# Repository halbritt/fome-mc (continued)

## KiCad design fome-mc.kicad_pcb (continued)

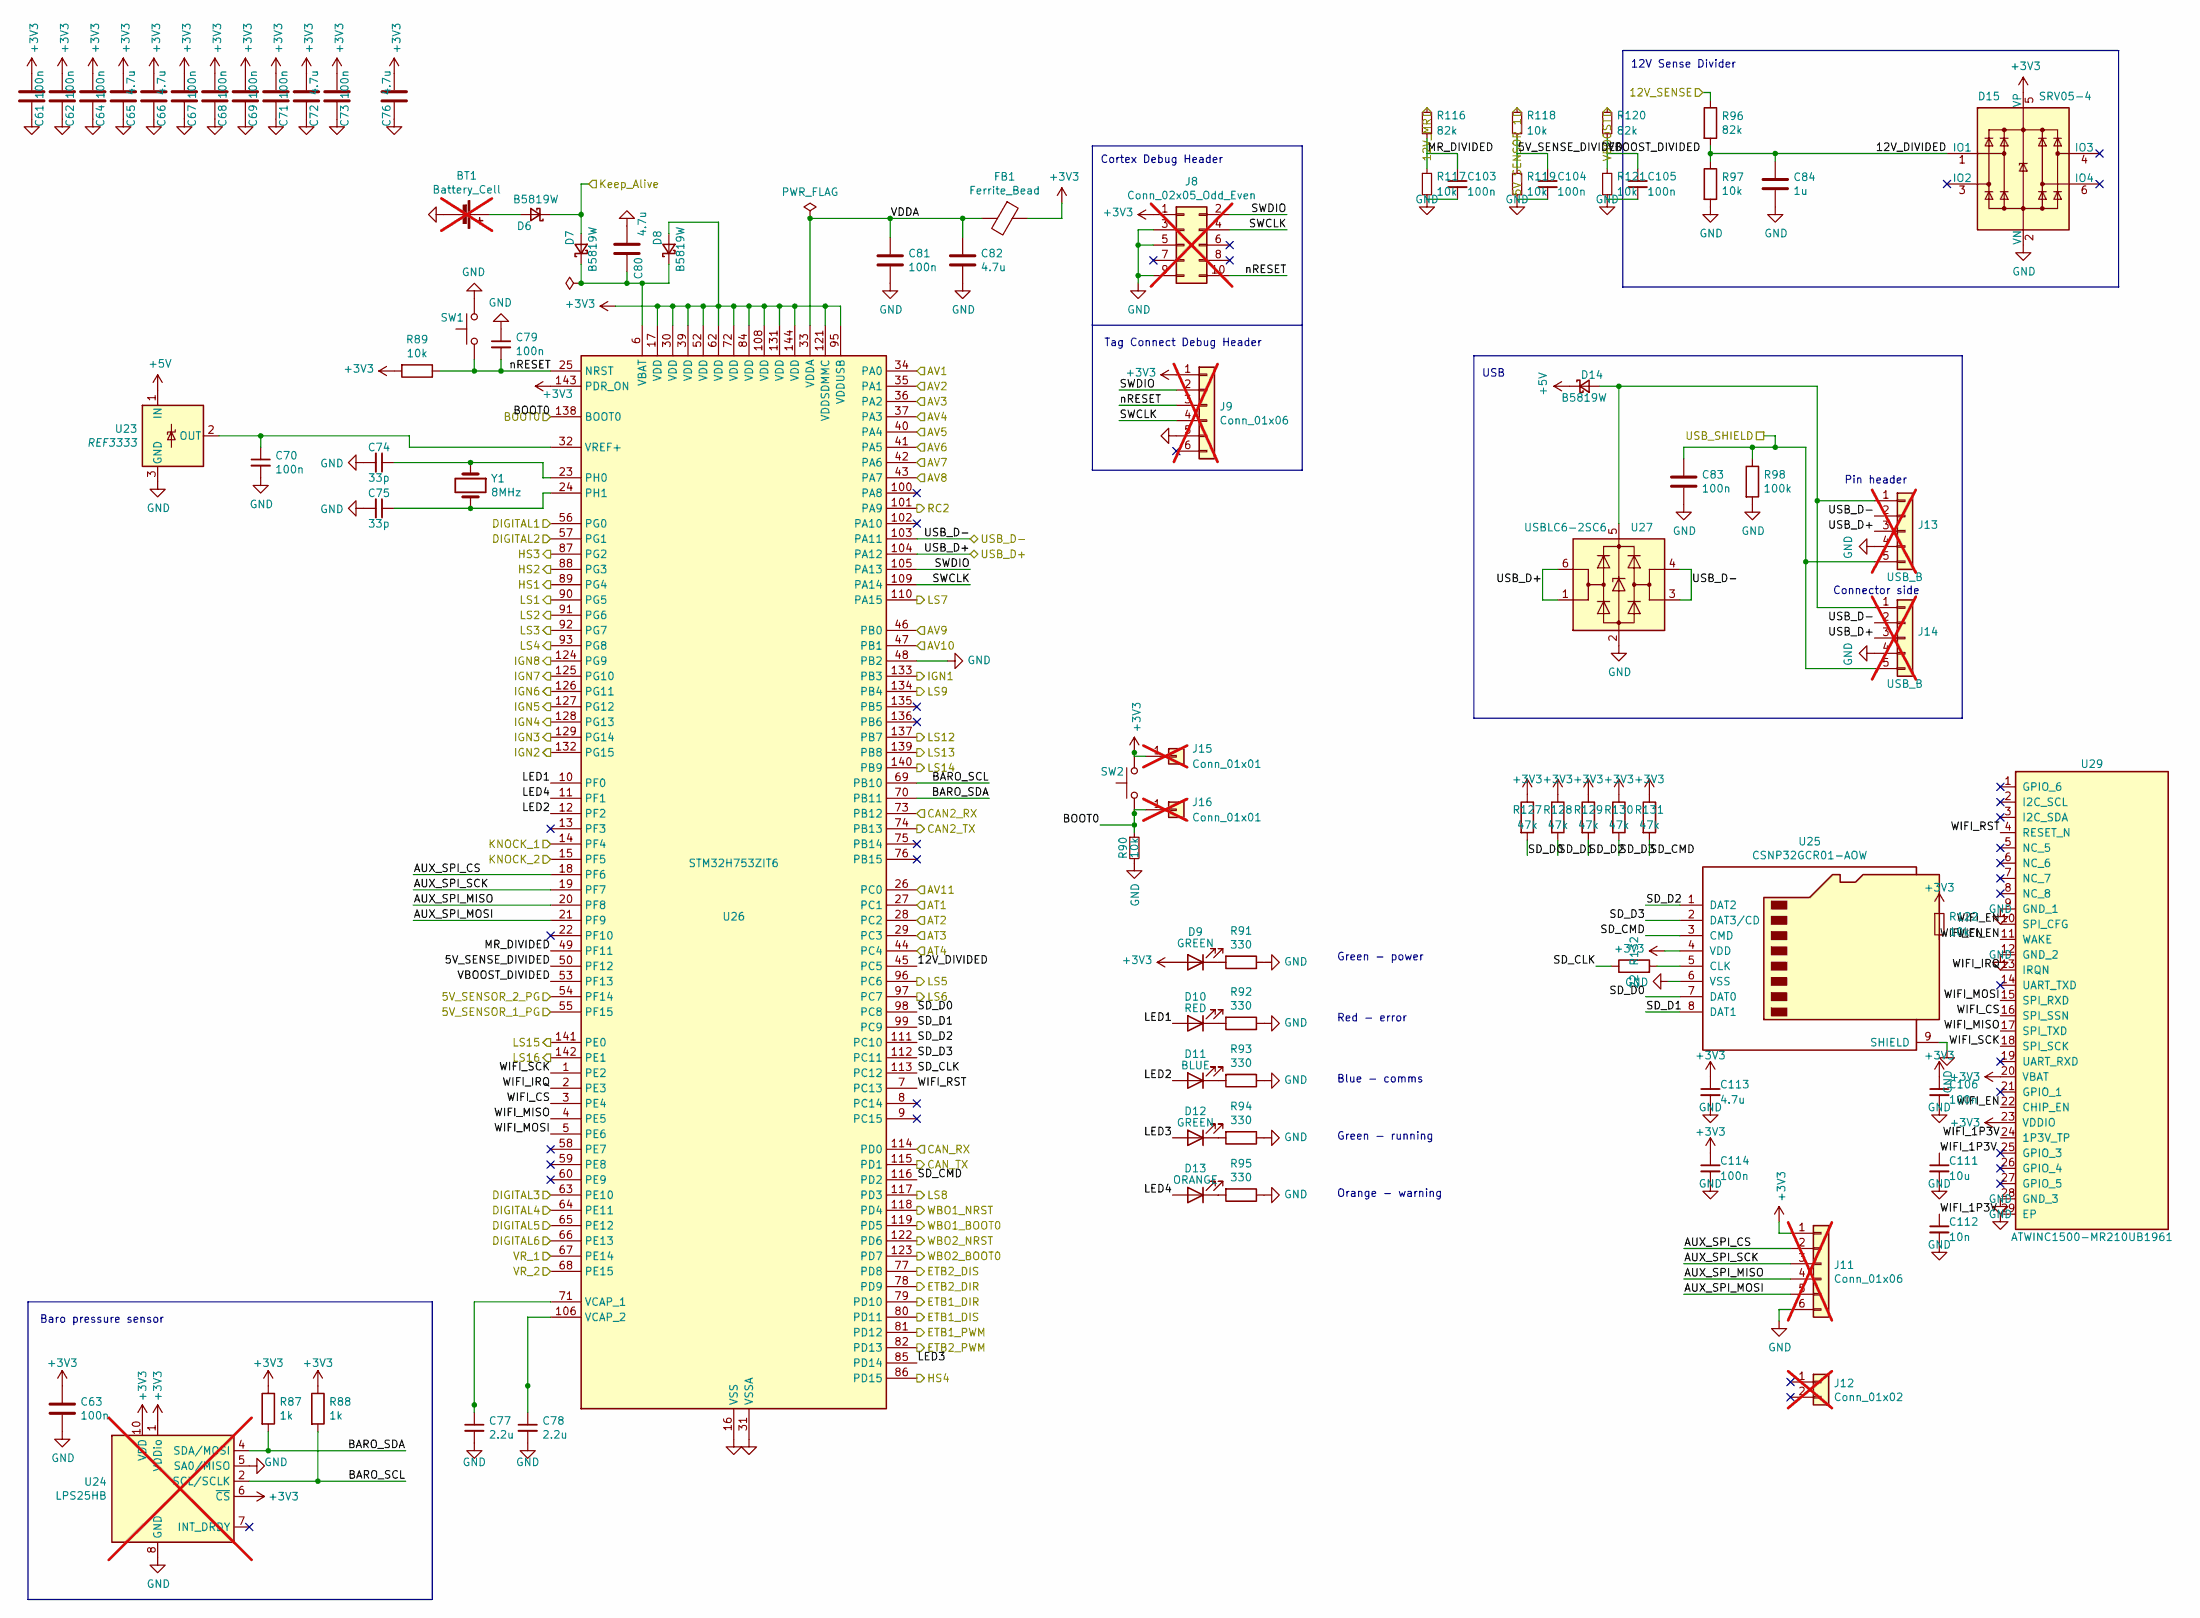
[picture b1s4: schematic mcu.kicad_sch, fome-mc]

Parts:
BT1: Battery_Cell; BatteryHolder_Keystone_1060_1x2032; not fitted
C61, C62, C63, C64, C67, C68, C69, C70, C71, C73, C79, C81, C83, C103, C104, C105, C106, C114: 100n; C_0603_1608Metric; LCSC C161115
C65, C66, C72, C76, C80, C82, C113: 4.7u; C_0603_1608Metric; LCSC C19666
C74, C75: 33p; C_0402_1005Metric; LCSC C1562
C77, C78: 2.2u; C_0603_1608Metric; LCSC C23630
C84: 1u; C_0603_1608Metric; LCSC C15849
C111: 10u; C_0603_1608Metric; LCSC C96446
C112: 10n; C_0603_1608Metric; LCSC C344025
D6, D7, D8, D14: B5819W; D_SOD-123; LCSC C8598
D9, D12: GREEN; LED_0603_1608Metric; LCSC C12624
D10: RED; LED_0603_1608Metric; LCSC C2286
D11: BLUE; LED_0603_1608Metric; LCSC C2288
D13: ORANGE; LED_0603_1608Metric; LCSC C2287
D15: SRV05-4; SOT-23-6; LCSC C85364
FB1: Ferrite_Bead; L_0805_2012Metric; LCSC C1015
J8: Conn_02x05_Odd_Even; PinHeader_2x05_P1.27mm_Vertical_SMD; LCSC N/A; not fitted
J9: Conn_01x06; Tag-Connect_TC2030-IDC-NL_2x03_P1.27mm_Vertical; not fitted
J11: Conn_01x06; PinHeader_1x06_P2.54mm_Vertical; LCSC N/A; not fitted
J12: Conn_01x02; PinHeader_1x02_P2.54mm_Vertical; LCSC N/A; not fitted
J13: USB_B; conn_5_2.5mm; LCSC N/A; not fitted
J14: USB_B; USB_B_TE_5787834_Vertical; LCSC N/A; not fitted
J15, J16: Conn_01x01; PinHeader_1x01_P2.54mm_Vertical; not fitted
R87, R88: 1k; R_0402_1005Metric; LCSC C11702
R89, R90, R97, R117, R118, R119, R121, R122: 10k; R_0402_1005Metric; LCSC C25744
R91, R92, R93, R94, R95: 330; R_0402_1005Metric; LCSC C25104
R96, R116, R120: 82k; R_0603_1608Metric; LCSC C23254
R98: 100k; R_0402_1005Metric; LCSC C25741
R127, R128, R129, R130, R131: 47k; R_0402_1005Metric; LCSC C25792
R132: 22; R_0603_1608Metric; LCSC C23345
SW1, SW2: SW_Push; SW_SPST_EVQQ2; LCSC C318887
U23: REF3333; SOT-23; LCSC C130016
U24: LPS25HB; ST_HLGA-10_2.5x2.5mm_P0.6mm_LayoutBorder3x2y; LCSC C87898; not fitted
U25: CSNP32GCR01-AOW; LGA-8_6x8mm_P1.25mm; LCSC C2841139
U26: STM32H753ZIT6; LQFP-144_20x20mm_P0.5mm; LCSC C730207
U27: USBLC6-2SC6; SOT-23-6; LCSC C7519
U29: ATWINC1500-MR210UB1961; ATWINC1500-MR210UB; LCSC C1558698
Y1: 8MHz; Crystal_SMD_5032-2Pin_5.0x3.2mm; LCSC C115962

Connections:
+3V3: C61.2, C62.2, C63.1, C64.2, C65.2, C66.2, C67.2, C68.2, C69.2, C71.2, C72.2, C73.2, C76.2, C106.1, C113.1, C114.1, D8.2 (A), D9.2 (A), D15.5 (VP), FB1.1, J8.1, J9.1, J11.1, J15.1, R87.1, R88.1, R89.2, R122.1, R127.1, R128.1, R129.1, R130.1, R131.1, SW2.2, U24.1 (VDDio), U24.6 (~CS), U24.10 (VDD), U25.4 (VDD), U26.17 (VDD), U26.30 (VDD), U26.39 (VDD), U26.52 (VDD), U26.62 (VDD), U26.72 (VDD), U26.84 (VDD), U26.95 (VDDUSB), U26.108 (VDD), U26.121 (VDDSDMMC), U26.131 (VDD), U26.143 (PDR_ON), U26.144 (VDD), U29.20 (VBAT), U29.23 (VDDIO); also elsewhere on the board
+5V: D14.1 (K), U23.1 (IN); also elsewhere on the board
/5V_SENSOR_1: R118.1; also elsewhere on the board
/12V_IGN_SW: R96.1; also elsewhere on the board
/12V_MR: R116.1; also elsewhere on the board
/BOOT0_NET: J16.1, R90.1, SW2.1, U26.138 (BOOT0); also elsewhere on the board
/ETB1_DIR: U26.79 (PD10); also elsewhere on the board
/ETB1_DIS: U26.80 (PD11); also elsewhere on the board
/ETB1_PWM: U26.81 (PD12); also elsewhere on the board
/ETB2_DIR: U26.78 (PD9); also elsewhere on the board
/ETB2_DIS: U26.77 (PD8); also elsewhere on the board
/ETB2_PWM: U26.82 (PD13); also elsewhere on the board
/Keep_Alive/Keep_Alive: D6.1 (K), D7.2 (A); also elsewhere on the board
/LS9: U26.134 (PB4); also elsewhere on the board
/LS12: U26.137 (PB7); also elsewhere on the board
/PB8_STEP_EN: U26.139 (PB8); also elsewhere on the board
/RC2: U26.101 (PA9); also elsewhere on the board
/USB_D+: J13.3, J14.3, U26.104 (PA12), U27.1 (I/O1), U27.6 (I/O1); also elsewhere on the board
/USB_D-: J13.2, J14.2, U26.103 (PA11), U27.3 (I/O2), U27.4 (I/O2); also elsewhere on the board
/VBOOST: R120.1; also elsewhere on the board
/WBO1_BOOT0: U26.119 (PD5); also elsewhere on the board
/WBO1_NRST: U26.118 (PD4); also elsewhere on the board
/WBO2_BOOT0: U26.123 (PD7); also elsewhere on the board
/WBO2_NRST: U26.122 (PD6); also elsewhere on the board
/highside_quad/IN1: U26.89 (PG4); also elsewhere on the board
/highside_quad/IN2: U26.88 (PG3); also elsewhere on the board
/highside_quad/IN3: U26.87 (PG2); also elsewhere on the board
/highside_quad/IN4: U26.86 (PD15); also elsewhere on the board
/ign1/IN1: U26.133 (PB3); also elsewhere on the board
/ign1/IN2: U26.132 (PG15); also elsewhere on the board
/ign1/IN3: U26.129 (PG14); also elsewhere on the board
/ign1/IN4: U26.128 (PG13); also elsewhere on the board
/ign2/IN1: U26.127 (PG12); also elsewhere on the board
/ign2/IN2: U26.126 (PG11); also elsewhere on the board
/ign2/IN3: U26.125 (PG10); also elsewhere on the board
/ign2/IN4: U26.124 (PG9); also elsewhere on the board
/knock/FILTERED_1: U26.14 (PF4); also elsewhere on the board
/knock/FILTERED_2: U26.15 (PF5); also elsewhere on the board
/lowside_quad1/IN1: U26.90 (PG5); also elsewhere on the board
/lowside_quad1/IN2: U26.91 (PG6); also elsewhere on the board
/lowside_quad1/IN3: U26.92 (PG7); also elsewhere on the board
/lowside_quad1/IN4: U26.93 (PG8); also elsewhere on the board
/lowside_quad2/IN1: U26.96 (PC6); also elsewhere on the board
/lowside_quad2/IN2: U26.97 (PC7); also elsewhere on the board
/lowside_quad2/IN3: U26.110 (PA15); also elsewhere on the board
/lowside_quad2/IN4: U26.117 (PD3); also elsewhere on the board
/lowside_quad4/IN2: U26.140 (PB9); also elsewhere on the board
/lowside_quad4/IN3: U26.141 (PE0); also elsewhere on the board
/lowside_quad4/IN4: U26.142 (PE1); also elsewhere on the board
/mcu/5V_SENSE_DIVIDED: C104.1, R118.2, R119.1, U26.50 (PF12)
/mcu/5V_SENSOR_1_PG: U26.55 (PF15); also elsewhere on the board
/mcu/5V_SENSOR_2_PG: U26.54 (PF14); also elsewhere on the board
/mcu/12V_DIVIDED: C84.1, D15.1 (IO1), R96.2, R97.1, U26.45 (PC5)
/mcu/AT1: U26.27 (PC1); also elsewhere on the board
/mcu/AT2: U26.28 (PC2); also elsewhere on the board
/mcu/AT3: U26.29 (PC3); also elsewhere on the board
/mcu/AT4: U26.44 (PC4); also elsewhere on the board
/mcu/AUX_SPI_CS: J11.2, U26.18 (PF6)
/mcu/AUX_SPI_MISO: J11.4, U26.20 (PF8)
/mcu/AUX_SPI_MOSI: J11.5, U26.21 (PF9)
/mcu/AUX_SPI_SCK: J11.3, U26.19 (PF7)
/mcu/AV1: U26.34 (PA0); also elsewhere on the board
/mcu/AV2: U26.35 (PA1); also elsewhere on the board
/mcu/AV3: U26.36 (PA2); also elsewhere on the board
/mcu/AV4: U26.37 (PA3); also elsewhere on the board
/mcu/AV5: U26.40 (PA4); also elsewhere on the board
/mcu/AV6: U26.41 (PA5); also elsewhere on the board
/mcu/AV7: U26.42 (PA6); also elsewhere on the board
/mcu/AV8: U26.43 (PA7); also elsewhere on the board
/mcu/AV9: U26.46 (PB0); also elsewhere on the board
/mcu/AV10: U26.47 (PB1); also elsewhere on the board
/mcu/AV11: U26.26 (PC0); also elsewhere on the board
/mcu/BARO_SCL: R88.2, U24.2 (SCL/SCLK), U26.69 (PB10)
/mcu/BARO_SDA: R87.2, U24.4 (SDA/MOSI), U26.70 (PB11)
/mcu/CAN2_RX: U26.73 (PB12); also elsewhere on the board
/mcu/CAN2_TX: U26.74 (PB13); also elsewhere on the board
/mcu/CAN_RX: U26.114 (PD0); also elsewhere on the board
/mcu/CAN_TX: U26.115 (PD1); also elsewhere on the board
/mcu/DIGITAL1: U26.56 (PG0); also elsewhere on the board
/mcu/DIGITAL2: U26.57 (PG1); also elsewhere on the board
/mcu/DIGITAL3: U26.63 (PE10); also elsewhere on the board
/mcu/DIGITAL4: U26.64 (PE11); also elsewhere on the board
/mcu/DIGITAL5: U26.65 (PE12); also elsewhere on the board
/mcu/DIGITAL6: U26.66 (PE13); also elsewhere on the board
/mcu/LED1: D10.2 (A), U26.10 (PF0)
/mcu/LED2: D11.2 (A), U26.12 (PF2)
/mcu/LED3: D12.2 (A), U26.85 (PD14)
/mcu/LED4: D13.2 (A), U26.11 (PF1)
/mcu/MR_DIVIDED: C103.1, R116.2, R117.1, U26.49 (PF11)
/mcu/SD_CLK: R132.1, U26.113 (PC12)
/mcu/SD_CMD: R131.2, U25.3 (CMD), U26.116 (PD2)
/mcu/SD_D0: R127.2, U25.7 (DAT0), U26.98 (PC8)
/mcu/SD_D1: R128.2, U25.8 (DAT1), U26.99 (PC9)
/mcu/SD_D2: R129.2, U25.1 (DAT2), U26.111 (PC10)
/mcu/SD_D3: R130.2, U25.2 (DAT3/CD), U26.112 (PC11)
/mcu/SWCLK: J8.4, J9.4, U26.109 (PA14)
/mcu/SWDIO: J8.2, J9.2, U26.105 (PA13)
/mcu/USB_SHIELD: C83.1, J13.5, J14.5, R98.1
/mcu/VBOOST_DIVIDED: C105.1, R120.2, R121.1, U26.53 (PF13)
/mcu/VDDA: C81.1, C82.1, FB1.2, U26.33 (VDDA)
/mcu/WIFI_1P3V: C111.1, C112.1, U29.24 (1P3V_TP)
/mcu/WIFI_CS: U26.3 (PE4), U29.16 (SPI_SSN)
/mcu/WIFI_EN: R122.2, U29.10 (SPI_CFG), U29.11 (WAKE), U29.22 (CHIP_EN)
/mcu/WIFI_IRQ: U26.2 (PE3), U29.13 (IRQN)
/mcu/WIFI_MISO: U26.4 (PE5), U29.17 (SPI_TXD)
/mcu/WIFI_MOSI: U26.5 (PE6), U29.15 (SPI_RXD)
/mcu/WIFI_RST: U26.7 (PC13), U29.4 (RESET_N)
/mcu/WIFI_SCK: U26.1 (PE2), U29.18 (SPI_SCK)
/mcu/nRESET: C79.2, J8.10, J9.3, R89.1, SW1.1, U26.25 (NRST)
unnamed: BT1.1 (+), D6.2 (A)
unnamed: C80.1, D7.1 (K), D8.1 (K), U26.6 (VBAT)
unnamed: D9.1 (K), R91.2
unnamed: D10.1 (K), R92.2
unnamed: D11.1 (K), R93.2
unnamed: D12.1 (K), R94.2
unnamed: D13.1 (K), R95.2
unnamed: D14.2 (A), J13.1, J14.1, U27.5 (VBUS)
unnamed: C70.1, U23.2 (OUT), U26.32 (VREF+)
unnamed: R132.2, U25.5 (CLK)
unnamed: C74.1, U26.23 (PH0), Y1.1
unnamed: C75.1, U26.24 (PH1), Y1.2
unnamed: C77.1, U26.71 (VCAP_1)
unnamed: C78.1, U26.106 (VCAP_2)

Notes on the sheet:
12V Sense Divider
Green - running
Green - power
Red - error
USB
Tag Connect Debug Header
Blue - comms
Orange - warning
Connector side
Pin header
Cortex Debug Header
Baro pressure sensor

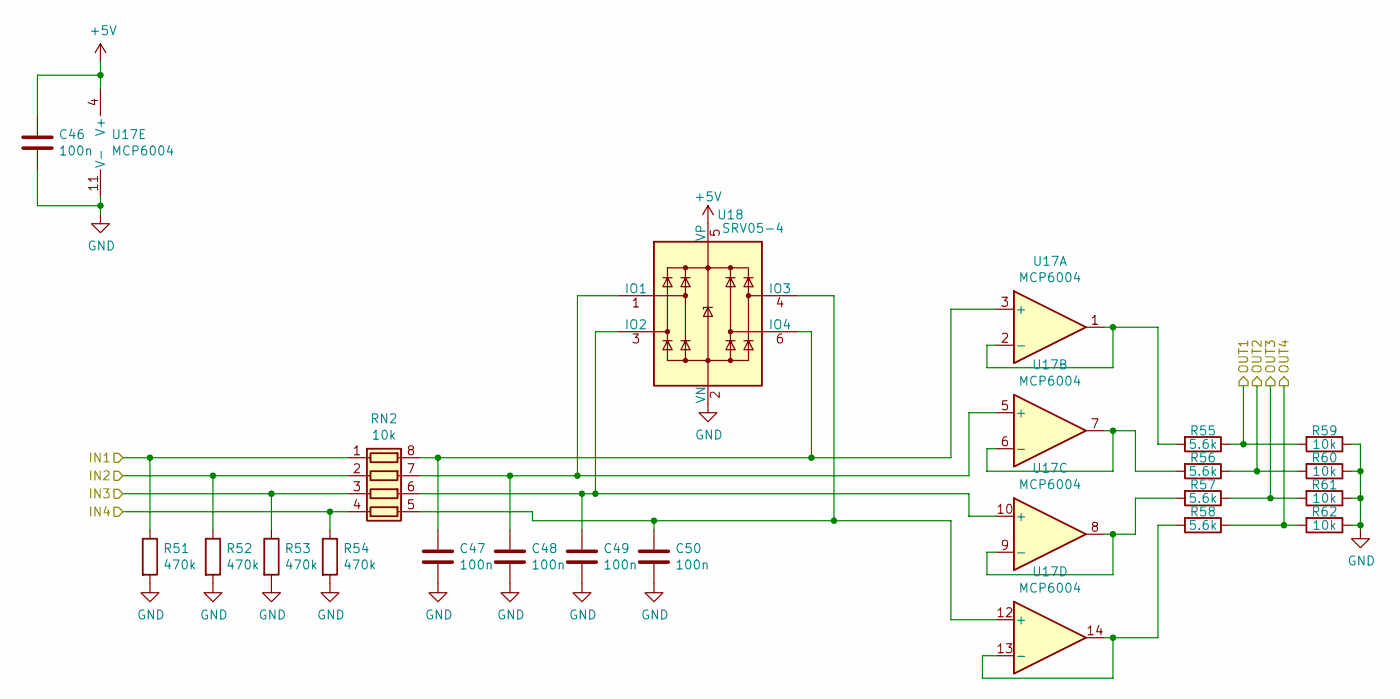
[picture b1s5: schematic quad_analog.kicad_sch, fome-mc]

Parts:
C46: 100n; C_0603_1608Metric; LCSC C161115
C47, C48, C49, C50: 100n; C_0402_1005Metric; LCSC C1525
R51, R52, R53, R54: 470k; R_0402_1005Metric; LCSC C25790
R55, R56, R57, R58: 5.6k; R_0402_1005Metric; LCSC C25908
R59, R60, R61, R62: 10k; R_0402_1005Metric; LCSC C25744
RN2: 10k; R_Array_Convex_4x0603; LCSC C29718
U17: MCP6004; TSSOP-14_4.4x5mm_P0.65mm; LCSC C50282
U18: SRV05-4; SOT-23-6; LCSC C85364

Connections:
+5V: C46.1, U17.4 (V+), U18.5 (VP); also elsewhere on the board
/AV1: R51.1, RN2.1 (R1.1); also elsewhere on the board
/AV2: R52.1, RN2.2 (R2.1); also elsewhere on the board
/AV3: R53.1, RN2.3 (R3.1); also elsewhere on the board
/AV4: R54.1, RN2.4 (R4.1); also elsewhere on the board
/mcu/AV1: R55.1, R59.2; also elsewhere on the board
/mcu/AV2: R56.1, R60.2; also elsewhere on the board
/mcu/AV3: R57.1, R61.2; also elsewhere on the board
/mcu/AV4: R58.1, R62.2; also elsewhere on the board
unnamed: C47.1, RN2.8 (R1.2), U17.3 (+), U18.6 (IO4)
unnamed: C48.1, RN2.7 (R2.2), U17.5 (+), U18.1 (IO1)
unnamed: C49.1, RN2.6 (R3.2), U17.10 (+), U18.3 (IO2)
unnamed: C50.1, RN2.5 (R4.2), U17.12 (+), U18.4 (IO3)
unnamed: R55.2, U17.1, U17.2 (-)
unnamed: R56.2, U17.6 (-), U17.7
unnamed: R57.2, U17.8, U17.9 (-)
unnamed: R58.2, U17.13 (-), U17.14

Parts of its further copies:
C51, C56: 100n; C_0603_1608Metric; LCSC C161115
C52, C53, C54, C55, C57, C58, C59, C60: 100n; C_0402_1005Metric; LCSC C1525
R63, R64, R65, R66, R75, R76, R77, R78: 470k; R_0402_1005Metric; LCSC C25790
R67, R68, R69, R70, R79, R80, R81, R82: 5.6k; R_0402_1005Metric; LCSC C25908
R71, R72, R73, R74, R83, R84, R85, R86: 10k; R_0402_1005Metric; LCSC C25744
RN3, RN4: 10k; R_Array_Convex_4x0603; LCSC C29718
U19, U21: MCP6004; TSSOP-14_4.4x5mm_P0.65mm; LCSC C50282
U20, U22: SRV05-4; SOT-23-6; LCSC C85364

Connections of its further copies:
+5V: C51.1, C56.1, U19.4 (V+), U20.5 (VP), U21.4 (V+), U22.5 (VP); also elsewhere on the board
/AV5: R63.1, RN3.1 (R1.1); also elsewhere on the board
/AV6: R64.1, RN3.2 (R2.1); also elsewhere on the board
/mcu/AV5: R67.1, R71.2; also elsewhere on the board
/mcu/AV6: R68.1, R72.2; also elsewhere on the board
/mcu/AV7: R69.1, R73.2; also elsewhere on the board
/mcu/AV8: R70.1, R74.2; also elsewhere on the board
/mcu/AV9: R79.1, R83.2; also elsewhere on the board
/mcu/AV10: R80.1, R84.2; also elsewhere on the board
/mcu/AV11: R81.1, R85.2; also elsewhere on the board
/quad_analog2/IN3: R65.1, RN3.3 (R3.1)
/quad_analog2/IN4: R66.1, RN3.4 (R4.1)
/quad_analog3/IN1: R75.1, RN4.1 (R1.1)
/quad_analog3/IN2: R76.1, RN4.2 (R2.1)
/quad_analog3/IN3: R77.1, RN4.3 (R3.1)
/quad_analog3/IN4: R78.1, RN4.4 (R4.1)
/quad_analog3/OUT4: R82.1, R86.2
unnamed: C52.1, RN3.8 (R1.2), U19.3 (+), U20.6 (IO4)
unnamed: C53.1, RN3.7 (R2.2), U19.5 (+), U20.1 (IO1)
unnamed: C54.1, RN3.6 (R3.2), U19.10 (+), U20.3 (IO2)
unnamed: C55.1, RN3.5 (R4.2), U19.12 (+), U20.4 (IO3)
unnamed: C57.1, RN4.8 (R1.2), U21.3 (+), U22.6 (IO4)
unnamed: C58.1, RN4.7 (R2.2), U21.5 (+), U22.1 (IO1)
unnamed: C59.1, RN4.6 (R3.2), U21.10 (+), U22.3 (IO2)
unnamed: C60.1, RN4.5 (R4.2), U21.12 (+), U22.4 (IO3)
unnamed: R67.2, U19.1, U19.2 (-)
unnamed: R68.2, U19.6 (-), U19.7
unnamed: R69.2, U19.8, U19.9 (-)
unnamed: R70.2, U19.13 (-), U19.14
unnamed: R79.2, U21.1, U21.2 (-)
unnamed: R80.2, U21.6 (-), U21.7
unnamed: R81.2, U21.8, U21.9 (-)
unnamed: R82.2, U21.13 (-), U21.14

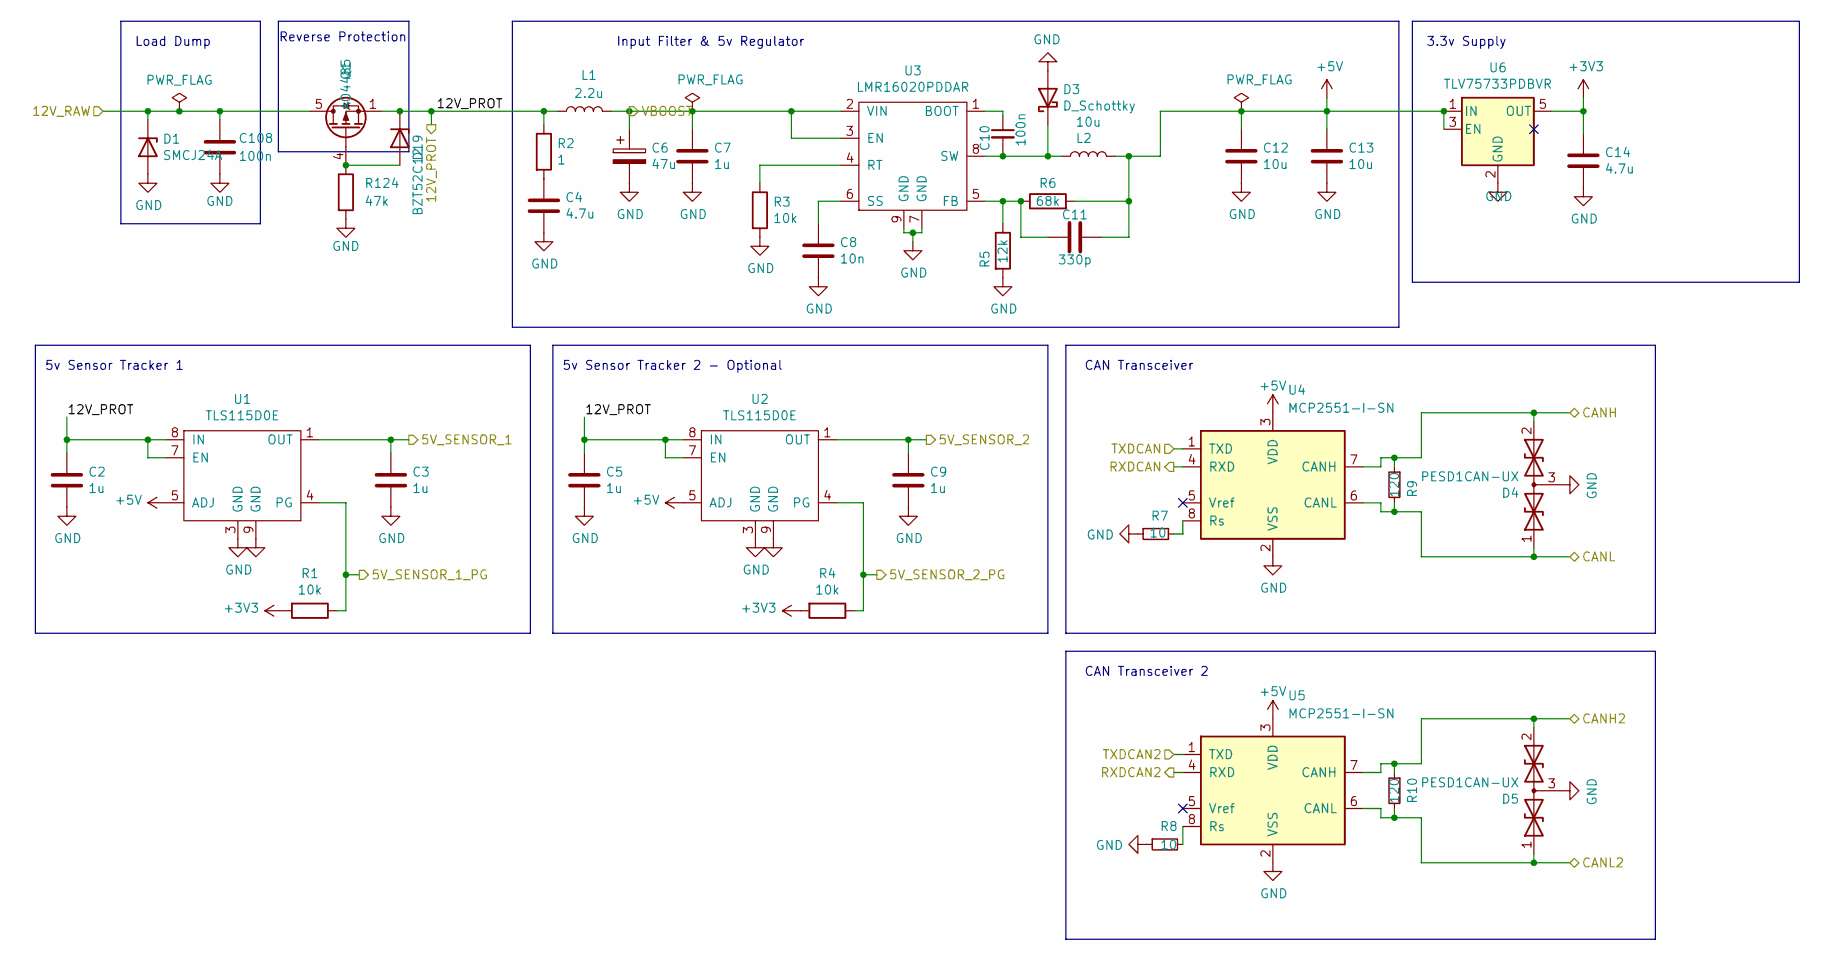
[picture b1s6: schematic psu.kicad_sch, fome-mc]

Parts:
C2, C5, C7: 1u; C_0805_2012Metric; LCSC C354368
C3, C9: 1u; C_0603_1608Metric; LCSC C15849
C4: 4.7u; C_1210_3225Metric; LCSC C417122
C6: 47u; CP_Elec_8x10.5; LCSC C454346
C8: 10n; C_0603_1608Metric; LCSC C344025
C10, C108: 100n; C_0603_1608Metric; LCSC C161115
C11: 330p; C_0402_1005Metric; LCSC C13533
C12: 10u; C_0603_1608Metric; LCSC C96446
C13: 10u; C_1206_3216Metric; LCSC C13585
C14: 4.7u; C_0603_1608Metric; LCSC C19666
D1: SMCJ24A; D_SMC; LCSC C224045
D3: D_Schottky; D_SMA; LCSC C8678
D4, D5: PESD1CAN-UX; SOT-323_SC-70; LCSC C907839
D19: BZT52C12; D_SOD-123; LCSC C43491
L1: 2.2u; L_1210_3225Metric; LCSC C2043220
L2: 10u; MWSA0503; LCSC C408412
Q1: AO4485; SOIC-8_3.9x4.9mm_P1.27mm; LCSC C51499
R1, R3, R4: 10k; R_0402_1005Metric; LCSC C25744
R2: 1; R_0402_1005Metric; LCSC C25086
R5: 12k; R_0402_1005Metric; LCSC C25752
R6: 68k; R_0402_1005Metric; LCSC C36871
R7, R8: 10; R_0603_1608Metric; LCSC C22859
R9, R10: 120; R_0603_1608Metric; LCSC C22787
R124: 47k; R_0603_1608Metric; LCSC C25819
U1, U2: TLS115D0E; Infineon_PG-DSO-8-43; LCSC C3747428
U3: LMR16020PDDAR; SOIC-8-1EP_3.9x4.9mm_P1.27mm_EP2.29x3mm; LCSC C190006
U4, U5: MCP2551-I-SN; SOIC-8_3.9x4.9mm_P1.27mm; LCSC C7376
U6: TLV75733PDBVR; SOT-23-5; LCSC C485517

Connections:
+3V3: C14.1, R1.2, R4.2, U6.5 (OUT); also elsewhere on the board
+5V: C11.1, C12.1, C13.1, L2.2, R6.2, U1.5 (ADJ), U2.5 (ADJ), U4.3 (VDD), U5.3 (VDD), U6.1 (IN), U6.3 (EN); also elsewhere on the board
/5V_SENSOR_1: C3.1, U1.1 (OUT); also elsewhere on the board
/5V_SENSOR_2: C9.1, U2.1 (OUT); also elsewhere on the board
/12V_PROT: C2.1, C5.1, D19.1 (K), L1.1, Q1.1 (S), Q1.2 (S), Q1.3 (S), R2.1, U1.7 (EN), U1.8 (IN), U2.7 (EN), U2.8 (IN)
/12V_RAW: C108.1, D1.1 (A1), Q1.5 (D), Q1.6 (D), Q1.7 (D), Q1.8 (D); also elsewhere on the board
/CAN2+: D5.2 (A2), R10.1, U5.7 (CANH); also elsewhere on the board
/CAN2-: D5.1 (A1), R10.2, U5.6 (CANL); also elsewhere on the board
/CAN+: D4.2 (A2), R9.1, U4.7 (CANH); also elsewhere on the board
/CAN-: D4.1 (A1), R9.2, U4.6 (CANL); also elsewhere on the board
/VBOOST: C6.1, C7.1, L1.2, U3.2 (VIN), U3.3 (EN); also elsewhere on the board
/mcu/5V_SENSOR_1_PG: R1.1, U1.4 (PG); also elsewhere on the board
/mcu/5V_SENSOR_2_PG: R4.1, U2.4 (PG); also elsewhere on the board
/mcu/CAN2_RX: U5.4 (RXD); also elsewhere on the board
/mcu/CAN2_TX: U5.1 (TXD); also elsewhere on the board
/mcu/CAN_RX: U4.4 (RXD); also elsewhere on the board
/mcu/CAN_TX: U4.1 (TXD); also elsewhere on the board
unnamed: C4.1, R2.2
unnamed: C10.2, D3.1 (K), L2.1, U3.8 (SW)
unnamed: D19.2 (A), Q1.4 (G), R124.1
unnamed: C10.1, U3.1 (BOOT)
unnamed: C11.2, R5.1, R6.1, U3.5 (FB)
unnamed: R3.1, U3.4 (RT)
unnamed: C8.1, U3.6 (SS)
unnamed: R7.2, U4.8 (Rs)
unnamed: R8.2, U5.8 (Rs)

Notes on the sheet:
5v Sensor Tracker 1
CAN Transceiver
Load Dump
Input Filter & 5v Regulator
Reverse Protection
3.3v Supply
5v Sensor Tracker 2 - Optional
CAN Transceiver 2

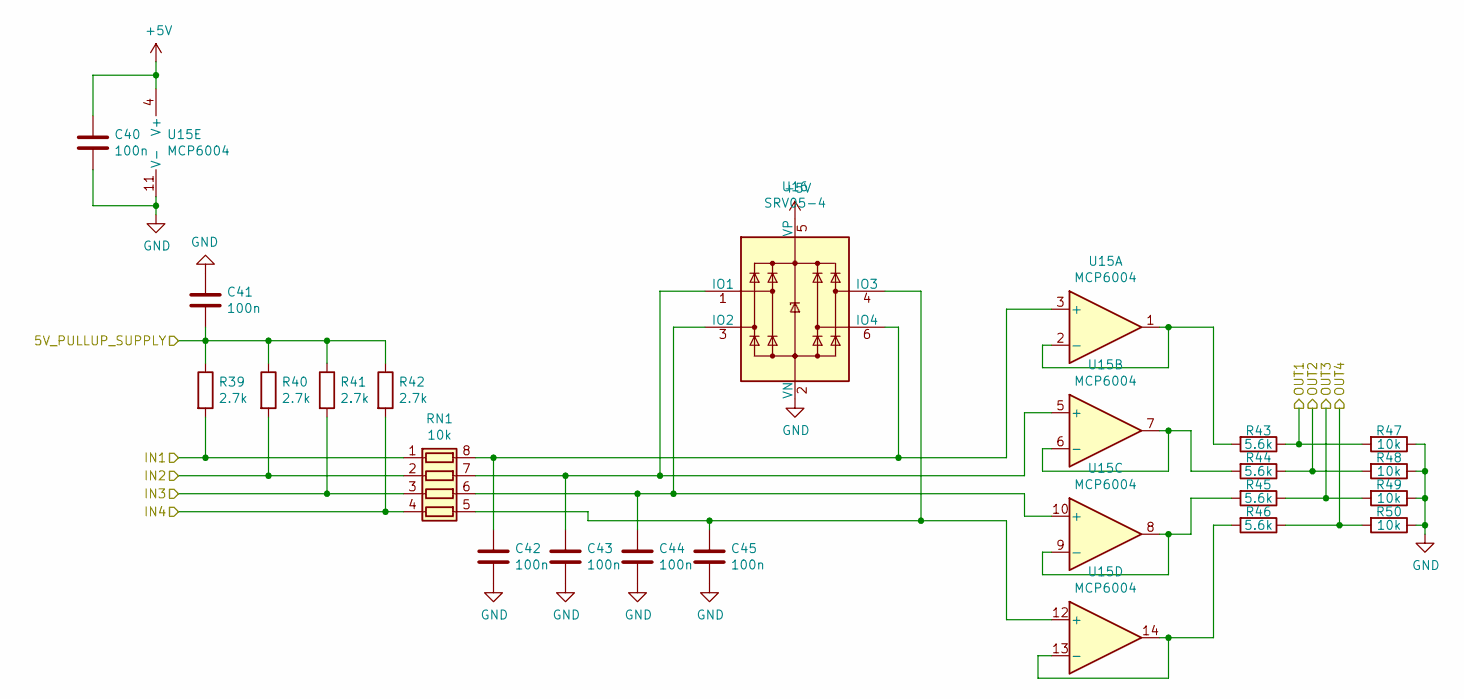
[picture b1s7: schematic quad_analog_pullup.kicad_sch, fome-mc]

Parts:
C40, C41: 100n; C_0603_1608Metric; LCSC C161115
C42, C43, C44, C45: 100n; C_0402_1005Metric; LCSC C1525
R39, R40, R41, R42: 2.7k; R_0603_1608Metric; LCSC C705760
R43, R44, R45, R46: 5.6k; R_0402_1005Metric; LCSC C25908
R47, R48, R49, R50: 10k; R_0402_1005Metric; LCSC C25744
RN1: 10k; R_Array_Convex_4x0603; LCSC C29718
U15: MCP6004; TSSOP-14_4.4x5mm_P0.65mm; LCSC C50282
U16: SRV05-4; SOT-23-6; LCSC C85364

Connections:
+5V: C40.1, U15.4 (V+), U16.5 (VP); also elsewhere on the board
/5V_SENSOR_1: C41.2, R39.1, R40.1, R41.1, R42.1; also elsewhere on the board
/AT1: R39.2, RN1.1 (R1.1); also elsewhere on the board
/AT2: R40.2, RN1.2 (R2.1); also elsewhere on the board
/mcu/AT1: R43.1, R47.2; also elsewhere on the board
/mcu/AT2: R44.1, R48.2; also elsewhere on the board
/mcu/AT3: R45.1, R49.2; also elsewhere on the board
/mcu/AT4: R46.1, R50.2; also elsewhere on the board
/quad_analog_temp/IN3: R41.2, RN1.3 (R3.1)
/quad_analog_temp/IN4: R42.2, RN1.4 (R4.1)
unnamed: C42.1, RN1.8 (R1.2), U15.3 (+), U16.6 (IO4)
unnamed: C43.1, RN1.7 (R2.2), U15.5 (+), U16.1 (IO1)
unnamed: C44.1, RN1.6 (R3.2), U15.10 (+), U16.3 (IO2)
unnamed: C45.1, RN1.5 (R4.2), U15.12 (+), U16.4 (IO3)
unnamed: R43.2, U15.1, U15.2 (-)
unnamed: R44.2, U15.6 (-), U15.7
unnamed: R45.2, U15.8, U15.9 (-)
unnamed: R46.2, U15.13 (-), U15.14

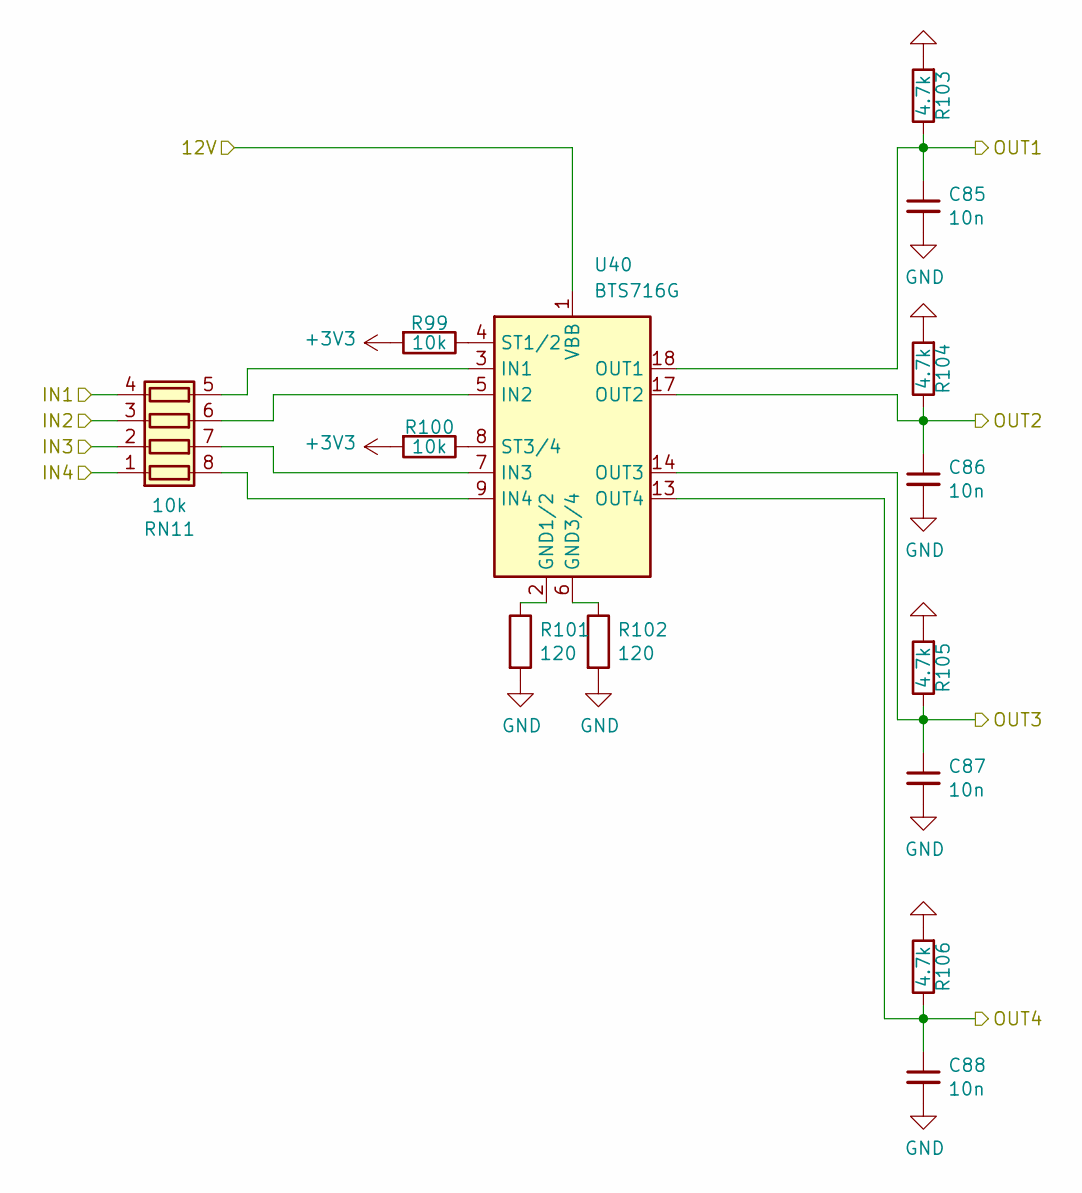
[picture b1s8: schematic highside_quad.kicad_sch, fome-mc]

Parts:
C85, C86, C87, C88: 10n; C_0603_1608Metric; LCSC C344025
R99, R100: 10k; R_0402_1005Metric; LCSC C25744
R101, R102: 120; R_0603_1608Metric; LCSC C22787
R103, R104, R105, R106: 4.7k; R_0805_2012Metric; LCSC C17673
RN11: 10k; R_Array_Convex_4x0603; LCSC C29718
U40: BTS716G; Infineon_PG-DSO-20-32; LCSC C85135

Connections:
+3V3: R99.2, R100.2; also elsewhere on the board
/12V_MR: U40.1 (VBB), U40.10 (VBB), U40.11 (VBB), U40.12 (VBB), U40.15 (VBB), U40.16 (VBB), U40.19 (VBB), U40.20 (VBB); also elsewhere on the board
/highside_quad/IN1: RN11.4 (R4.1); also elsewhere on the board
/highside_quad/IN2: RN11.3 (R3.1); also elsewhere on the board
/highside_quad/IN3: RN11.2 (R2.1); also elsewhere on the board
/highside_quad/IN4: RN11.1 (R1.1); also elsewhere on the board
/highside_quad/OUT1: C85.1, R103.1, U40.18 (OUT1)
/highside_quad/OUT2: C86.1, R104.1, U40.17 (OUT2)
/highside_quad/OUT3: C87.1, R105.1, U40.14 (OUT3)
/highside_quad/OUT4: C88.1, R106.1, U40.13 (OUT4)
unnamed: RN11.8 (R1.2), U40.9 (IN4)
unnamed: RN11.7 (R2.2), U40.7 (IN3)
unnamed: RN11.6 (R3.2), U40.5 (IN2)
unnamed: RN11.5 (R4.2), U40.3 (IN1)
unnamed: R101.1, U40.2 (GND1/2)
unnamed: R102.1, U40.6 (GND3/4)
unnamed: R99.1, U40.4 (ST1/2)
unnamed: R100.1, U40.8 (ST3/4)

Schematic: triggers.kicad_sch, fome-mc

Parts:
C24, C25, C26, C27, C28, C29, C30, C31, C32, C33, C34, C35, C36, C37: 1n; C_0603_1608Metric; LCSC C1588
C38, C39: 100n; C_0603_1608Metric; LCSC C161115
C109, C110: 100n; C_0402_1005Metric; LCSC C1525
R23, R24, R25, R26, R27, R28, R29, R30, R31, R32, R33, R34: 2.7k; R_0603_1608Metric; LCSC C705760
R35, R36, R37, R38, R125, R126: 10k; R_0402_1005Metric; LCSC C25744
U8, U9, U10: SN74LVC2G17DB; SOT-23-6; LCSC C10429
U11, U12: SRV05-4; SOT-23-6; LCSC C85364
U13, U14: MAX9924UAUB+; MSOP-10_3x3mm_P0.5mm; LCSC C143633

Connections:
+3V3: R125.1, R126.1, U8.5 (VCC), U9.5 (VCC), U10.5 (VCC); also elsewhere on the board
+5V: U11.5 (VP), U12.5 (VP); also elsewhere on the board
/5V_SENSOR_1: C38.2, C39.2, C109.1, C110.1, R23.1, R24.1, R25.1, R26.1, R27.1, R28.1, U13.10 (VCC), U14.10 (VCC); also elsewhere on the board
/DIGITAL_1: C24.1, R23.2, R29.2; also elsewhere on the board
/DIGITAL_2: C25.1, R24.2, R30.2; also elsewhere on the board
/DIGITAL_3: C26.1, R25.2, R31.2; also elsewhere on the board
/DIGITAL_4: C27.1, R26.2, R32.2; also elsewhere on the board
/VR1+: R35.1; also elsewhere on the board
/VR1-: R36.1; also elsewhere on the board
/VR2+: R37.1; also elsewhere on the board
/VR2-: R38.1; also elsewhere on the board
/mcu/DIGITAL1: U10.6; also elsewhere on the board
/mcu/DIGITAL2: U8.6; also elsewhere on the board
/mcu/DIGITAL3: U8.4; also elsewhere on the board
/mcu/DIGITAL4: U9.6; also elsewhere on the board
/mcu/DIGITAL5: U10.4; also elsewhere on the board
/mcu/DIGITAL6: U9.4; also elsewhere on the board
/triggers/HALL_IN_5: C28.1, R27.2, R33.2
/triggers/HALL_IN_6: C29.1, R28.2, R34.2
unnamed: C33.1, R32.1, U9.1, U11.1 (IO1), U11.6 (IO4)
unnamed: C35.1, R34.1, U9.3, U11.3 (IO2), U11.4 (IO3)
unnamed: C34.1, R33.1, U10.3, U12.1 (IO1)
unnamed: C30.1, R29.1, U10.1, U12.3 (IO2)
unnamed: C31.1, R30.1, U8.1, U12.4 (IO3)
unnamed: C32.1, R31.1, U8.3, U12.6 (IO4)
unnamed: C36.1, R35.2, U13.1 (IN+)
unnamed: C36.2, R36.2, U13.2 (IN-)
unnamed: C37.1, R37.2, U14.1 (IN+)
unnamed: C37.2, R38.2, U14.2 (IN-)

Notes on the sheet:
74HC parts include internal clamp diodes to the power rails

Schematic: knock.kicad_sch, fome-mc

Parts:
C15: 10n; C_0603_1608Metric; LCSC C344025
C16, C17: 3.3n; C_0805_2012Metric; LCSC C472819
C18, C19: 680p; C_0603_1608Metric; LCSC C1630
C20, C21: 330p; C_0402_1005Metric; LCSC C13533
C22, C23: 47p; C_0402_1005Metric; LCSC C1567
JP1, JP2: Jumper_NO_Small; SolderJumper-2_P1.3mm_Open_TrianglePad1.0x1.5mm; LCSC N/A; not fitted
R11, R12, R21, R22: 33k; R_0402_1005Metric; LCSC C25779
R13, R14, R19, R20: 100k; R_0402_1005Metric; LCSC C25741
R15, R16: 470k; R_0402_1005Metric; LCSC C25790
R17, R18: 12k; R_0402_1005Metric; LCSC C25752
U7: MCP6004; TSSOP-14_4.4x5mm_P0.65mm; LCSC C50282

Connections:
+3V3: R11.2, U7.4 (V+); also elsewhere on the board
/KNOCK_1: C16.2, JP1.1; also elsewhere on the board
/KNOCK_2: C17.2, JP2.1; also elsewhere on the board
/knock/FILTERED_1: C20.2, U7.6 (-), U7.7; also elsewhere on the board
/knock/FILTERED_2: C21.2, U7.8, U7.9 (-); also elsewhere on the board
/knock/V_mid: C15.2, R11.1, R12.1, U7.3 (+), U7.12 (+)
unnamed: C16.1, JP1.2, R13.2
unnamed: C17.1, JP2.2, R14.2
unnamed: C18.2, R17.1, R19.2
unnamed: C19.2, R18.1, R20.2
unnamed: C20.1, R19.1, R21.2
unnamed: C21.1, R20.1, R22.2
unnamed: R15.1, R17.2, U7.1
unnamed: R16.1, R18.2, U7.14
unnamed: R13.1, R15.2, U7.2 (-)
unnamed: C22.2, R21.1, U7.5 (+)
unnamed: C23.2, R22.1, U7.10 (+)
unnamed: R14.1, R16.2, U7.13 (-)

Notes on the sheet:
Short jumper if DC is interesting

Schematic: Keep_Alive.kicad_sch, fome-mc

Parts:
C89: 100n; C_0603_1608Metric; LCSC C161115
C90: 2.2u; C_0603_1608Metric; LCSC C23630
D16, D17: B5819W; D_SOD-123; LCSC C8598
D20, D21: B340A-13-F; D_SMA; LCSC C85098
D22: SMCJ24A; D_SMC; LCSC C224045
IC1: PSM712-LF-T7; SOT-23; Manufacturer_Part_Number PSM712-LF-T7; LCSC C32677
R107: 4.7k; R_0805_2012Metric; LCSC C17673
U41: MIC5205-3.3YM5; SOT-23-5; LCSC C37970

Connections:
/12V_IGN_SW: D20.2 (A); also elsewhere on the board
/12V_MR: D21.2 (A), D22.1 (K); also elsewhere on the board
/12V_RAW: D20.1 (K), D21.1 (K); also elsewhere on the board
/Keep_Alive/Keep_Alive: D17.1 (K); also elsewhere on the board
/Perm_Live: D16.2 (A); also elsewhere on the board
unnamed: D16.1 (K), R107.1
unnamed: C90.2, D17.2 (A), U41.5 (OUT)
unnamed: C89.1, IC1.1 (I/O_1), R107.2, U41.1 (IN), U41.3 (EN)

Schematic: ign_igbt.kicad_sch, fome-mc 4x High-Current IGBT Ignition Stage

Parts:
Q201, Q202, Q203, Q204: FGD3040G2-F085; TO-252-2; LCSC C606124
R201, R202, R203, R204: 15R; R_0603_1608Metric; LCSC C22810
R205, R206, R207, R208: 10k; R_0402_1005Metric; LCSC C25744

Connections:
/IGN1: R201.1; also elsewhere on the board
/IGN1_COIL: Q201.2 (C); also elsewhere on the board
/IGN2: R202.1; also elsewhere on the board
/IGN2_COIL: Q202.2 (C); also elsewhere on the board
/IGN3: R203.1; also elsewhere on the board
/IGN3_COIL: Q203.2 (C); also elsewhere on the board
/IGN4: R204.1; also elsewhere on the board
/IGN4_COIL: Q204.2 (C); also elsewhere on the board
unnamed: Q201.1 (G), R201.2, R205.1
unnamed: Q202.1 (G), R202.2, R206.1
unnamed: Q203.1 (G), R203.2, R207.1
unnamed: Q204.1 (G), R204.2, R208.1
